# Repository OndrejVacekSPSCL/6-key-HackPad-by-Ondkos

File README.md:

# 6-key HackPad by Ondkos

This MacroPad was made for [Hackclub Hackpad](https://hackpad.hackclub.com). 

It's a 6-key macropad witch uses XIAO RB2040. It also has  2 LEDs and runs on KMK. It is upgraded version of the [tutorial one](https://hackpad.hackclub.com/guide).

Through the process of making this one, I beceme interested in PCB design and all the stuff around the hackpad. I don't have much time now (because of school), but durning the summer holidays I would like to try to make entire keyboard (with keys in matrix) 

### Chalanges
I had never used KMK or QMK before. I tried QMK but then eventually decided that KMK was easier to understand and use.

## PCB
Here's my PCB! It was made in KiCad. Because it only has 6 keys, it doesn't use matrix to make it easier.

#### Schematic

#### PCB

## CAD Model:

It has 2 separate printed pieces. The bottom is where everthing is housed, and the top secures the PCB in place. It has big hole so you can see the electronics (not the best decision, I know).

Made in Fusion360.

## Key mapping

It can do anything that you like, but at this point it does this

| Keys | Action |
| :--- | :--- |
| <kbd>1st</kbd> | Makes screenshot |
| <kbd>2nd</kbd> | Delete |
| <kbd>3rd</kbd> | Testing macro |
| <kbd>4th</kbd> | < |
| <kbd>5th</kbd> | > |
| <kbd>6th</kbd> | Restart hackpad |

## Specifications

BOM: 
- 6x Cherry MX Switches
- 2x SK6812 MINI Leds
- 1x [XIAO RP2040](https://wiki.seeedstudio.com/XIAO-RP2040/)
- 6x Blank DSA Keycaps
- 4x M3x16 Bolt
- 4x M3 Heatset

Others:
- [KMK Firmware](https://github.com/OndrejVacekSPSCL/6-key-HackPad-by-Ondkos/blob/main/production/main.py)
- [Top.step](https://github.com/OndrejVacekSPSCL/6-key-HackPad-by-Ondkos/blob/main/production/Top.step)
- [Bottom.step](https://github.com/OndrejVacekSPSCL/6-key-HackPad-by-Ondkos/blob/main/production/Bottom.step)
- [Custom PCB](https://github.com/OndrejVacekSPSCL/6-key-HackPad-by-Ondkos/blob/main/PCB)

#### Cool HackPads by other HackClubers
[RoyTyper](https://github.com/hackclub/hackpad/tree/main/hackpads/RoyTyper)

[1 Up Hackpad](https://github.com/hackclub/hackpad/tree/main/hackpads/1-Up-Hackpad)

[B-Deck](https://github.com/hackclub/hackpad/tree/main/hackpads/B-Deck)

[Minecraft Circle Hotbar](https://github.com/hackclub/hackpad/tree/main/hackpads/MinecraftCircleHotbar)

[Macro Pad V.1](https://github.com/hackclub/hackpad/tree/main/hackpads/Macro%20Pad%20V.1)

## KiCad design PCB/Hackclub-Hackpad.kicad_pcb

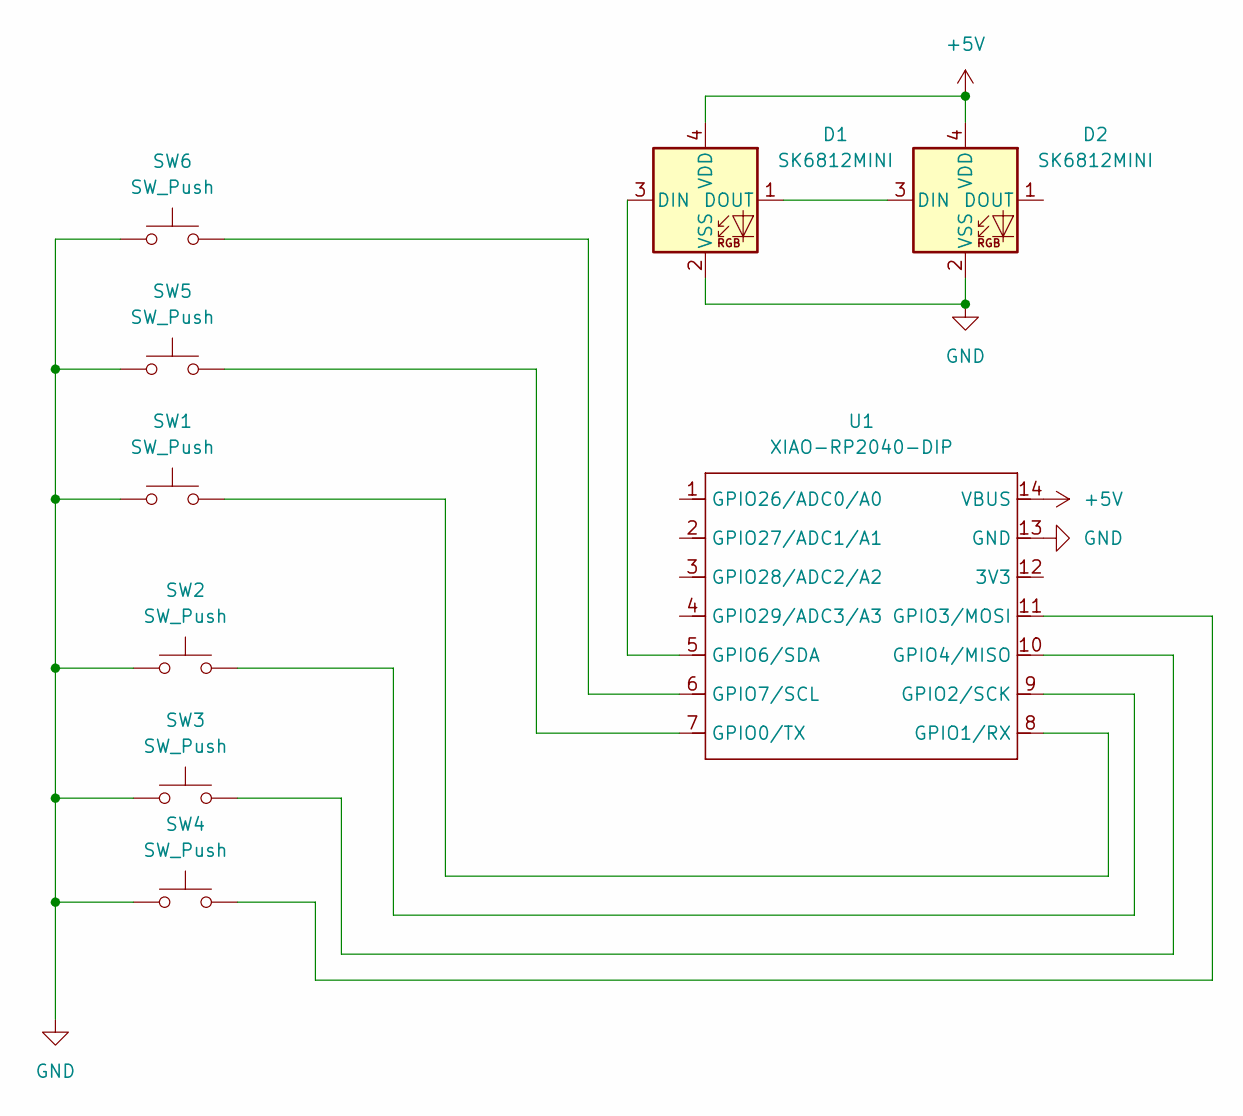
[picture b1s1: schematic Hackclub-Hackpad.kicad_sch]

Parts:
D1, D2: SK6812MINI; LED_SK6812MINI_PLCC4_3.5x3.5mm_P1.75mm
SW1, SW2, SW3, SW4, SW5, SW6: SW_Push; SW_Cherry_MX_1.00u_PCB
U1: XIAO-RP2040-DIP

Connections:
+5V: D1.4 (VDD), D2.4 (VDD), U1.14 (VBUS)
GND: D1.2 (VSS), D2.2 (VSS), SW1.1, SW2.1, SW3.1, SW4.1, SW5.1, SW6.1, U1.13 (GND)
unnamed: D1.3 (DIN), U1.5 (GPIO6/SDA)
unnamed: D1.1 (DOUT), D2.3 (DIN)
unnamed: SW5.2, U1.7 (GPIO0/TX)
unnamed: SW1.2, U1.8 (GPIO1/RX)
unnamed: SW2.2, U1.9 (GPIO2/SCK)
unnamed: SW4.2, U1.11 (GPIO3/MOSI)
unnamed: SW3.2, U1.10 (GPIO4/MISO)
unnamed: SW6.2, U1.6 (GPIO7/SCL)

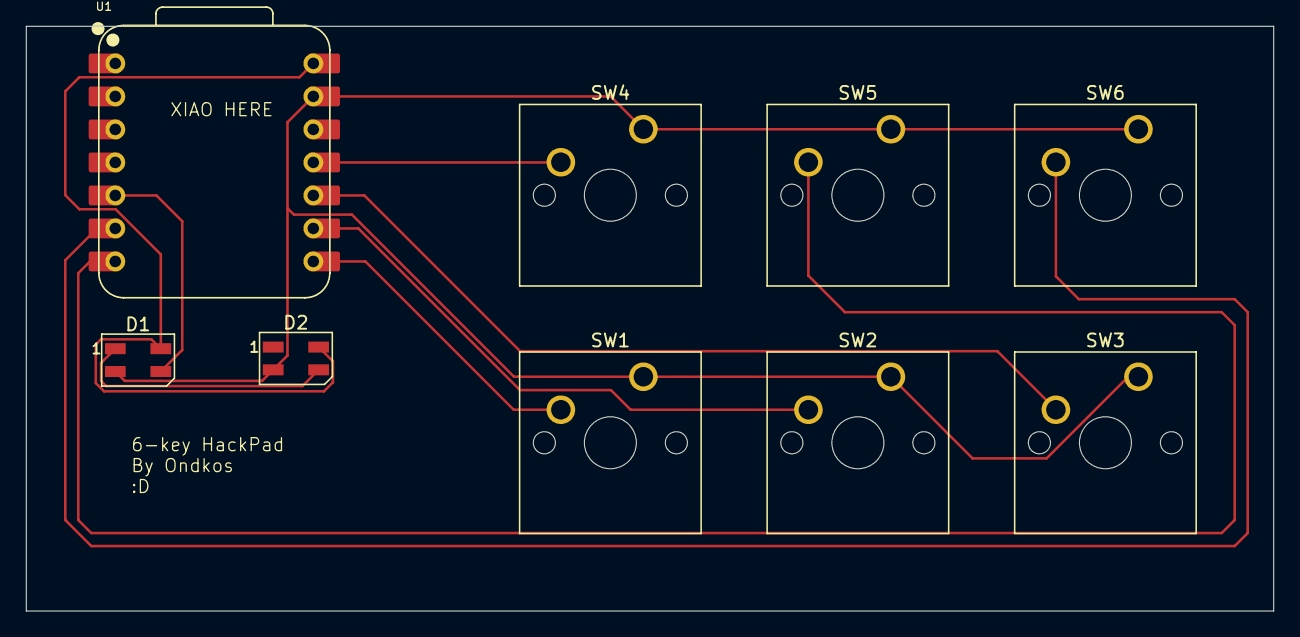
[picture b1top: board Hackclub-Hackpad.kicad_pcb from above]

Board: 2 copper layers, 96.0 x 45.0 mm, 9 parts (0 on the bottom side), 10 nets.

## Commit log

2025-05-21 InitialCommit
2025-05-21 moved files to KiCad folder
2025-05-21 Created case
2025-05-21 files structure edit
2025-05-21 .gitignore update
2025-05-22 Finished CAD files
2025-05-22 deleted .gitignore; added assets folder
2025-05-22 Deleted pcb .step
